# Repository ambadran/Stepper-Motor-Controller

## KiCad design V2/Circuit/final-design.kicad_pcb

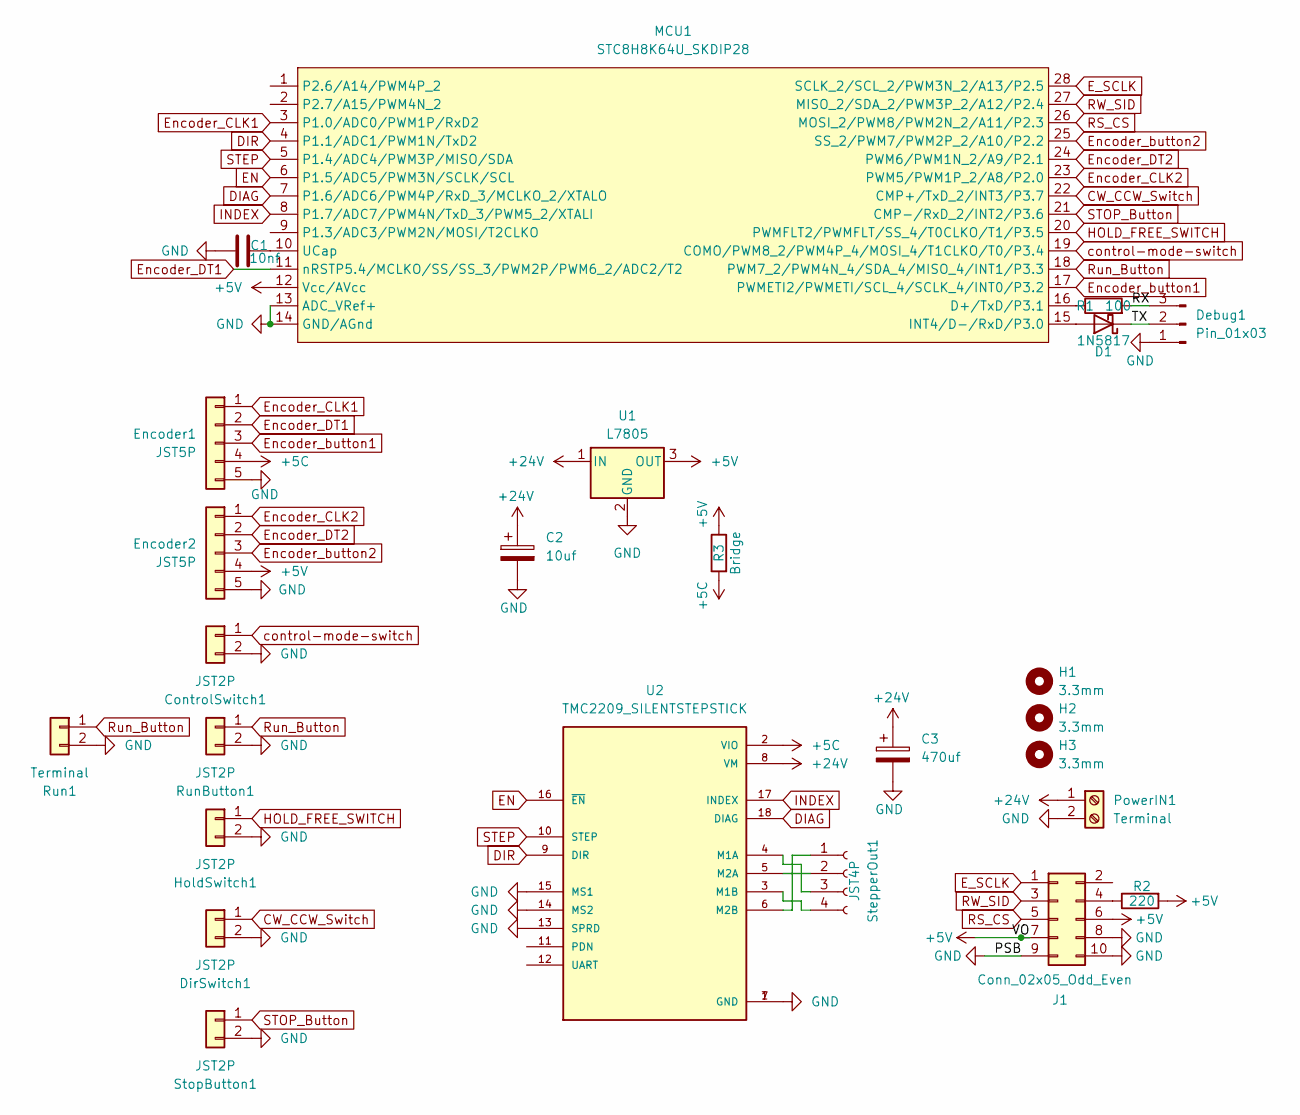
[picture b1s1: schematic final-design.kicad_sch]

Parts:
C1: 10nf; R_Axial_DIN0207_L6.3mm_D2.5mm_P7.62mm_Horizontal
C2: 10uf; CP_Radial_D5.0mm_P2.50mm
C3: 470uf; CP_Radial_D8.0mm_P3.50mm
ControlSwitch1: JST2P; JST_EH_B2B-EH-A_1x02_P2.50mm_Vertical
D1: 1N5817; D_DO-41_SOD81_P7.62mm_Horizontal
Debug1: Pin_01x03; PinHeader_1x03_P2.54mm_Vertical
DirSwitch1: JST2P; JST_EH_B2B-EH-A_1x02_P2.50mm_Vertical
Encoder1, Encoder2: JST5P; JST_EH_B5B-EH-A_1x05_P2.50mm_Vertical
H1, H2, H3: 3.3mm; MountingHole_3.2mm_M3
HoldSwitch1: JST2P; JST_EH_B2B-EH-A_1x02_P2.50mm_Vertical
J1: Conn_02x05_Odd_Even; IDC-Header_2x05_P2.54mm_Vertical
MCU1: STC8H8K64U_SKDIP28; SKDIP28
PowerIN1: Terminal; TerminalBlock_bornier-2_P5.08mm
R1: 100; R_Axial_DIN0207_L6.3mm_D2.5mm_P7.62mm_Horizontal
R2: 220; R_Axial_DIN0207_L6.3mm_D2.5mm_P7.62mm_Horizontal
R3: Bridge; R_Axial_DIN0207_L6.3mm_D2.5mm_P5.08mm_Vertical
Run1: Terminal; TerminalBlock_bornier-2_P5.08mm
RunButton1: JST2P; JST_EH_B2B-EH-A_1x02_P2.50mm_Vertical
StepperOut1: JST4P; JST_EH_B4B-EH-A_1x04_P2.50mm_Vertical
StopButton1: JST2P; JST_EH_B2B-EH-A_1x02_P2.50mm_Vertical
U1: L7805; TO-220-3_Vertical
U2: TMC2209_SILENTSTEPSTICK; MODULE_TMC2209_SILENTSTEPSTICK; PARTREV 1.20

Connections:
+5C: Encoder1.4, R3.2, U2.2 (VIO)
+5V: Encoder2.4, J1.6, J1.7, MCU1.12 (Vcc/AVcc), R2.2, R3.1, U1.3 (OUT)
+24V: C2.1, C3.1, PowerIN1.1, U1.1 (IN), U2.8 (VM)
/RX: Debug1.3, R1.2
/TX: D1.1 (K), Debug1.2
CW_CCW_Switch: DirSwitch1.1, MCU1.22 (CMP+/TxD_2/INT3/P3.7)
DIAG: MCU1.7 (P1.6/ADC6/PWM4P/RxD_3/MCLKO_2/XTALO), U2.18 (DIAG)
DIR: MCU1.4 (P1.1/ADC1/PWM1N/TxD2), U2.9 (DIR)
EN: MCU1.6 (P1.5/ADC5/PWM3N/SCLK/SCL), U2.16 (~EN)
E_SCLK: J1.1, MCU1.28 (SCLK_2/SCL_2/PWM3N_2/A13/P2.5)
Encoder_CLK1: Encoder1.1, MCU1.3 (P1.0/ADC0/PWM1P/RxD2)
Encoder_CLK2: Encoder2.1, MCU1.23 (PWM5/PWM1P_2/A8/P2.0)
Encoder_DT1: Encoder1.2, MCU1.11 (nRSTP5.4/MCLKO/SS/SS_3/PWM2P/PWM6_2/ADC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)
Encoder_DT2: Encoder2.2, MCU1.24 (PWM6/PWM1N_2/A9/P2.1)
Encoder_button1: Encoder1.3, MCU1.17 (PWMETI2/PWMETI/SCL_4/SCLK_4/INT0/P3.2)
Encoder_button2: Encoder2.3, MCU1.25 (SS_2/PWM7/PWM2P_2/A10/P2.2)
GND: C1.1, C2.2, C3.2, ControlSwitch1.2, Debug1.1, DirSwitch1.2, Encoder1.5, Encoder2.5, HoldSwitch1.2, J1.8, J1.9, J1.10, MCU1.13 (ADC_VRef+), MCU1.14 (GND/AGnd), PowerIN1.2, Run1.2, RunButton1.2, StopButton1.2, U1.2 (GND), U2.1 (GND), U2.7 (GND), U2.13 (SPRD), U2.14 (MS2), U2.15 (MS1)
HOLD_FREE_SWITCH: HoldSwitch1.1, MCU1.20 (PWMFLT2/PWMFLT/SS_4/T0CLKO/T1/P3.5)
INDEX: MCU1.8 (P1.7/ADC7/PWM4N/TxD_3/PWM5_2/XTALI), U2.17 (INDEX)
unnamed: D1.2 (A), MCU1.15 (INT4/D-/RxD/P3.0)
unnamed: J1.4, R2.1
unnamed: MCU1.16 (D+/TxD/P3.1), R1.1
unnamed: C1.2, MCU1.10 (UCap)
unnamed: StepperOut1.1, U2.6 (M2B)
unnamed: StepperOut1.2, U2.5 (M2A)
unnamed: StepperOut1.3, U2.4 (M1A)
unnamed: StepperOut1.4, U2.3 (M1B)
RS_CS: J1.5, MCU1.26 (MOSI_2/PWM8/PWM2N_2/A11/P2.3)
RW_SID: J1.3, MCU1.27 (MISO_2/SDA_2/PWM3P_2/A12/P2.4)
Run_Button: MCU1.18 (PWM7_2/PWM4N_4/SDA_4/MISO_4/INT1/P3.3), Run1.1, RunButton1.1
STEP: MCU1.5 (P1.4/ADC4/PWM3P/MISO/SDA), U2.10 (STEP)
STOP_Button: MCU1.21 (CMP-/RxD_2/INT2/P3.6), StopButton1.1
control-mode-switch: ControlSwitch1.1, MCU1.19 (COMO/PWM8_2/PWM4P_4/MOSI_4/T1CLKO/T0/P3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)

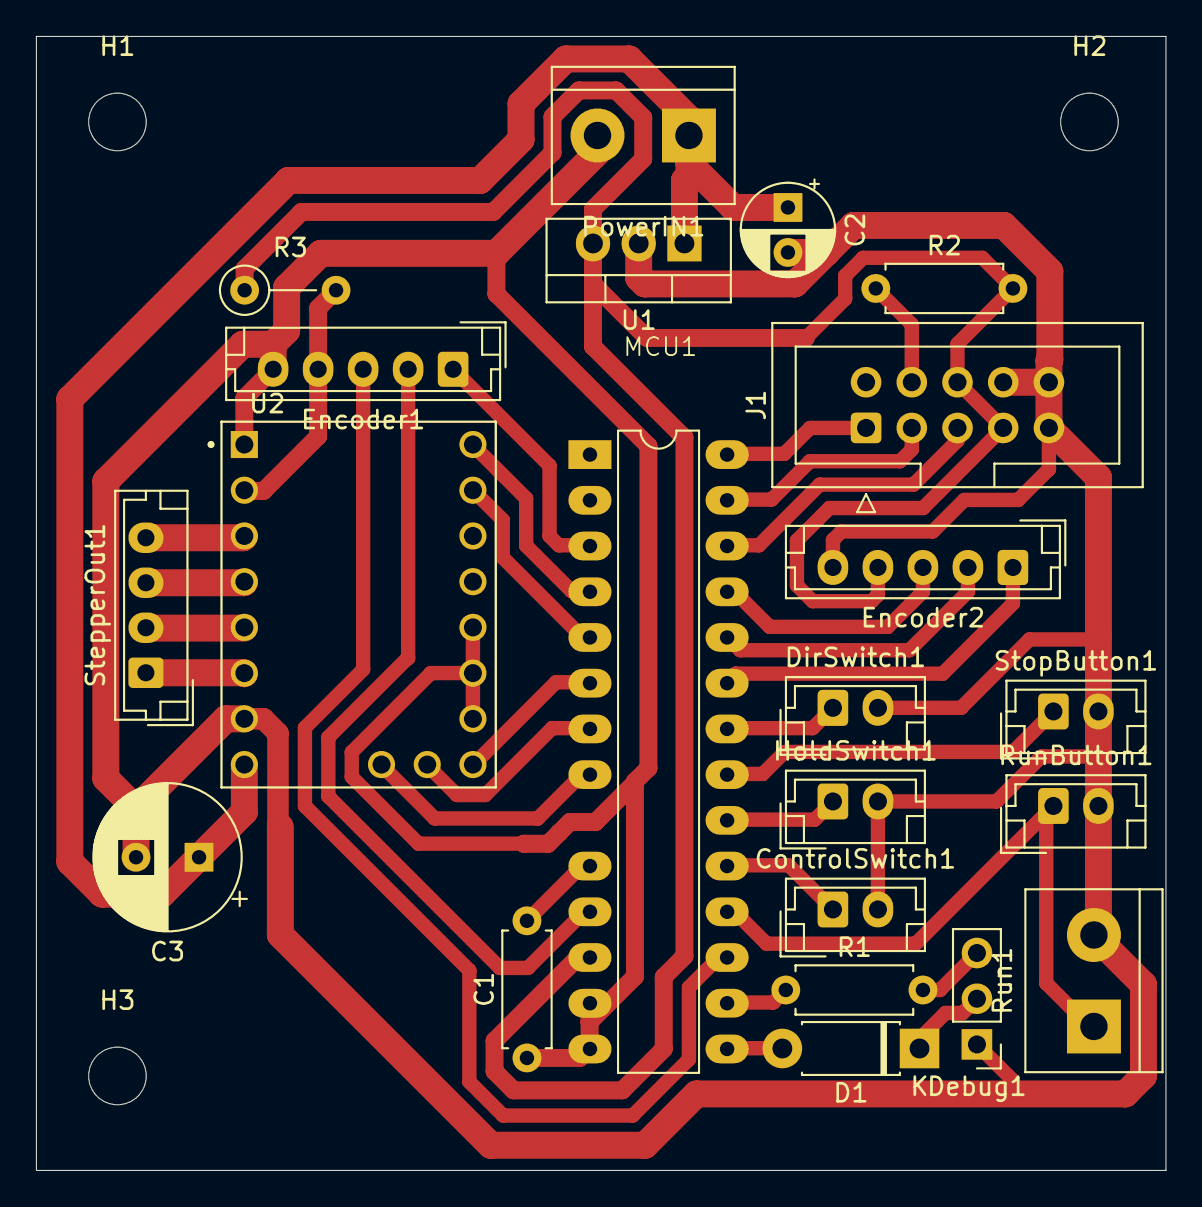
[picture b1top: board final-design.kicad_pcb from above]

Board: 2 copper layers, 62.8 x 63.0 mm, 25 parts (0 on the bottom side), 33 nets.

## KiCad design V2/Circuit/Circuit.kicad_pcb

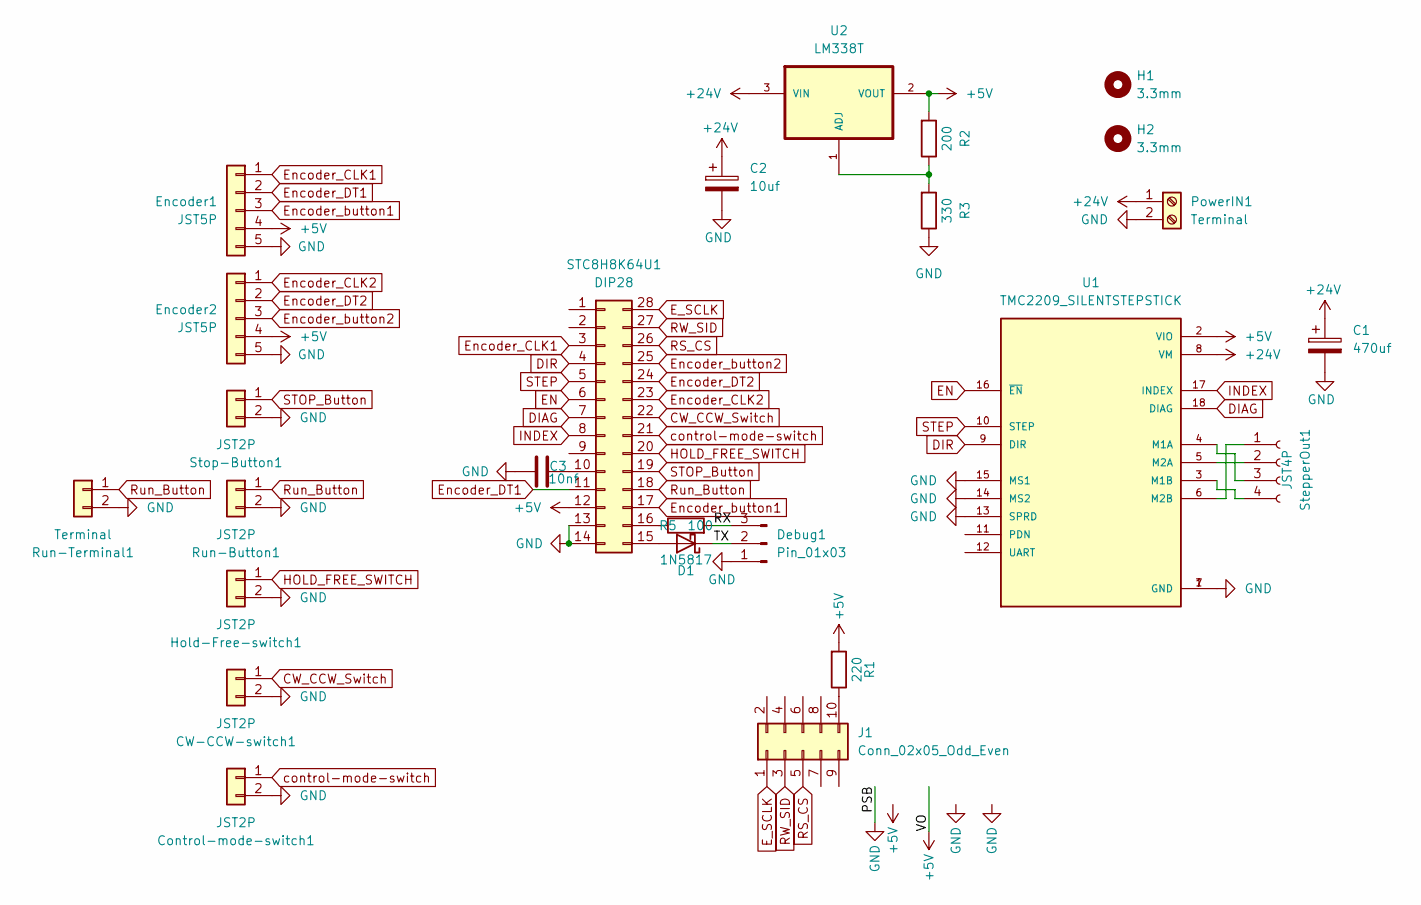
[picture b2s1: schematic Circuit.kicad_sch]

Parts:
C1: 470uf; CP_Radial_D8.0mm_P3.50mm
C2: 10uf; CP_Radial_D5.0mm_P2.50mm
C3: 10nf; R_Axial_DIN0207_L6.3mm_D2.5mm_P7.62mm_Horizontal
CW-CCW-switch1: JST2P; JST_EH_B2B-EH-A_1x02_P2.50mm_Vertical
Control-mode-switch1: JST2P; JST_EH_B2B-EH-A_1x02_P2.50mm_Vertical
D1: 1N5817; D_DO-41_SOD81_P7.62mm_Horizontal
Debug1: Pin_01x03; PinHeader_1x03_P2.54mm_Vertical
Encoder1, Encoder2: JST5P; JST_EH_B5B-EH-A_1x05_P2.50mm_Vertical
H1, H2: 3.3mm; MountingHole_3.2mm_M3
Hold-Free-switch1: JST2P; JST_EH_B2B-EH-A_1x02_P2.50mm_Vertical
J1: Conn_02x05_Odd_Even; IDC-Header_2x05_P2.54mm_Vertical
PowerIN1: Terminal; TerminalBlock_bornier-2_P5.08mm
R1: 220; R_Axial_DIN0207_L6.3mm_D2.5mm_P7.62mm_Horizontal
R2: 200; R_Axial_DIN0207_L6.3mm_D2.5mm_P7.62mm_Horizontal
R3: 330; R_Axial_DIN0207_L6.3mm_D2.5mm_P7.62mm_Horizontal
R5: 100; R_Axial_DIN0207_L6.3mm_D2.5mm_P7.62mm_Horizontal
Run-Button1: JST2P; JST_EH_B2B-EH-A_1x02_P2.50mm_Vertical
Run-Terminal1: Terminal; TerminalBlock_bornier-2_P5.08mm
STC8H8K64U1: DIP28; DIP-28_W7.62mm_Socket_LongPads
StepperOut1: JST4P; JST_EH_B4B-EH-A_1x04_P2.50mm_Vertical
Stop-Button1: JST2P; JST_EH_B2B-EH-A_1x02_P2.50mm_Vertical
U1: TMC2209_SILENTSTEPSTICK; MODULE_TMC2209_SILENTSTEPSTICK; PARTREV 1.20
U2: LM338T; TO254P1054X470X1955-3

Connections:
+5V: Encoder1.4, Encoder2.4, R1.2, R2.2, STC8H8K64U1.12, U1.2 (VIO), U2.2 (VOUT); also elsewhere on the board
+24V: C1.1, C2.1, PowerIN1.1, U1.8 (VM), U2.3 (VIN)
/RX: Debug1.3, R5.2
/TX: D1.1 (K), Debug1.2
CW_CCW_Switch: CW-CCW-switch1.1, STC8H8K64U1.22
DIAG: STC8H8K64U1.7, U1.18 (DIAG)
DIR: STC8H8K64U1.4, U1.9 (DIR)
EN: STC8H8K64U1.6, U1.16 (~EN)
E_SCLK: J1.1, STC8H8K64U1.28; also elsewhere on the board
Encoder_CLK1: Encoder1.1, STC8H8K64U1.3
Encoder_CLK2: Encoder2.1, STC8H8K64U1.23
Encoder_DT1: Encoder1.2, STC8H8K64U1.11
Encoder_DT2: Encoder2.2, STC8H8K64U1.24
Encoder_button1: Encoder1.3, STC8H8K64U1.17
Encoder_button2: Encoder2.3, STC8H8K64U1.25
GND: C1.2, C2.2, C3.1, CW-CCW-switch1.2, Control-mode-switch1.2, Debug1.1, Encoder1.5, Encoder2.5, Hold-Free-switch1.2, PowerIN1.2, R3.1, Run-Button1.2, Run-Terminal1.2, STC8H8K64U1.13, STC8H8K64U1.14, Stop-Button1.2, U1.1 (GND), U1.7 (GND), U1.13 (SPRD), U1.14 (MS2), U1.15 (MS1); also elsewhere on the board
HOLD_FREE_SWITCH: Hold-Free-switch1.1, STC8H8K64U1.20
INDEX: STC8H8K64U1.8, U1.17 (INDEX)
unnamed: D1.2 (A), STC8H8K64U1.15
unnamed 19: J1.10, R1.1; also elsewhere on the board
unnamed: C3.2, STC8H8K64U1.10
unnamed: R5.1, STC8H8K64U1.16
unnamed: StepperOut1.1, U1.6 (M2B)
unnamed: StepperOut1.2, U1.5 (M2A)
unnamed: StepperOut1.3, U1.4 (M1A)
unnamed: StepperOut1.4, U1.3 (M1B)
unnamed: R2.1, R3.2, U2.1 (ADJ)
RS_CS: J1.5, STC8H8K64U1.26; also elsewhere on the board
RW_SID: J1.3, STC8H8K64U1.27; also elsewhere on the board
Run_Button: Run-Button1.1, Run-Terminal1.1, STC8H8K64U1.18
STEP: STC8H8K64U1.5, U1.10 (STEP)
STOP_Button: STC8H8K64U1.19, Stop-Button1.1
control-mode-switch: Control-mode-switch1.1, STC8H8K64U1.21

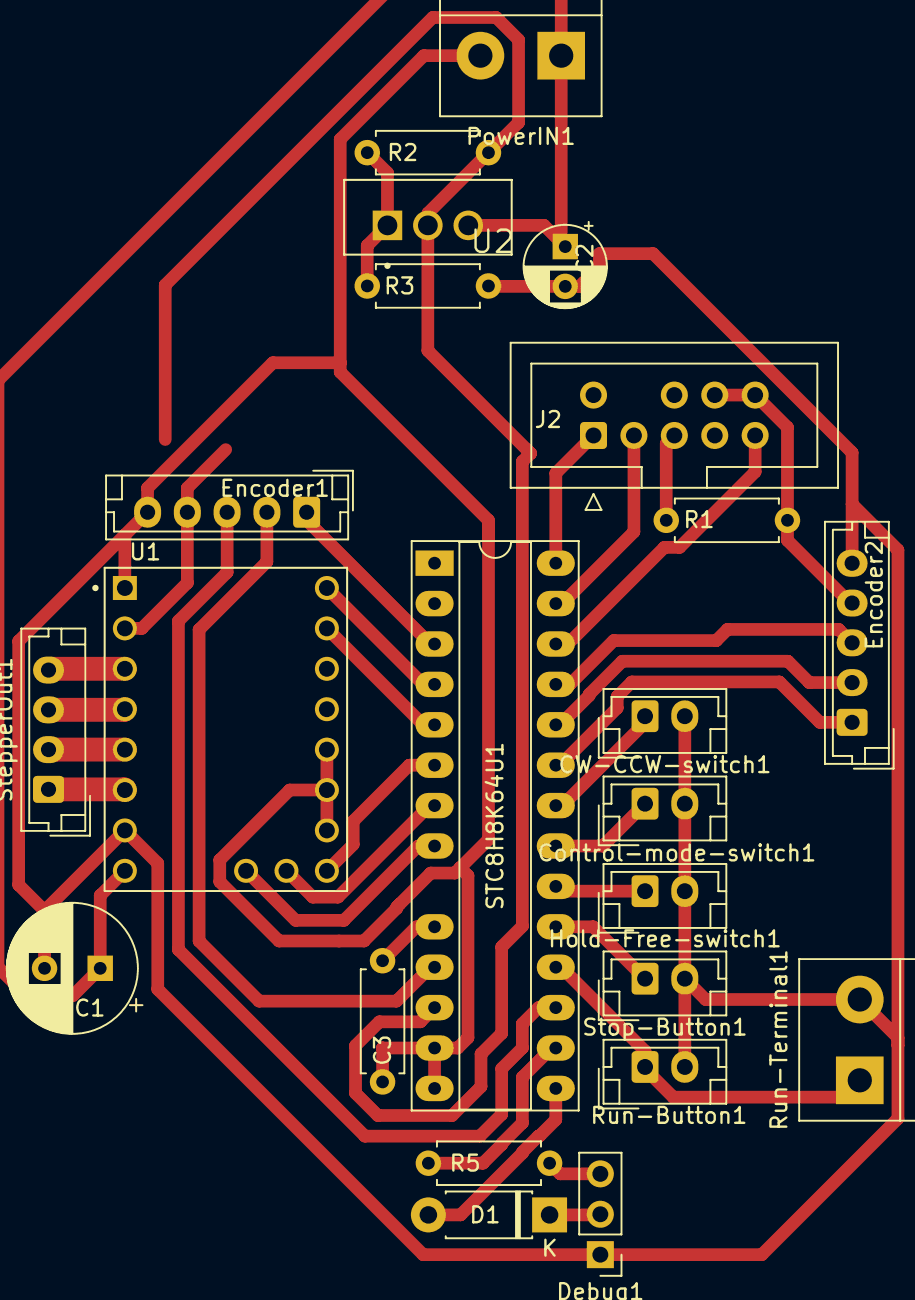
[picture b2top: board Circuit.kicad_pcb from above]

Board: 2 copper layers, 25 parts (0 on the bottom side), 33 nets.

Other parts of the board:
J2: IDC-10P; IDC-Header_2x05_P2.54mm_Vertical

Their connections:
+5V: J2.8, J2.10; also elsewhere on the board
E_SCLK: J2.1; also elsewhere on the board
GND: J2.2, J2.6, J2.7; also elsewhere on the board
unnamed 19: J2.5; also elsewhere on the board
RS_CS: J2.9; also elsewhere on the board
RW_SID: J2.3; also elsewhere on the board

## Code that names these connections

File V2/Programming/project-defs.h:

#ifndef PROJECT_DEFS
#define PROJECT_DEFS

/* Console settings */
#define CONSOLE_SPEED 115200
#define CONSOLE_UART UART1
#define CONSOLE_PIN_CONFIG 0

/* gpio-hal Settings */
// ***Right Side Pins Mappings*** //
#define E_SCLK_PORT GPIO_PORT2
#define E_SCLK_PIN GPIO_PIN5
#define RW_SID_PORT GPIO_PORT2
#define RW_SID_PIN GPIO_PIN4
#define RS_CS_PORT GPIO_PORT2
#define RS_CS_PIN GPIO_PIN3
#define ENCODER2_BUTTON_PORT GPIO_PORT2
#define ENCODER2_BUTTON_PIN GPIO_PIN2
#define ENCODER2_DT_PORT GPIO_PORT2
#define ENCODER2_DT_PIN GPIO_PIN1
#define ENCODER2_CLK_PORT GPIO_PORT2
#define ENCODER2_CLK_PIN GPIO_PIN0
#define CW_CCW_SWITCH_PORT GPIO_PORT3
#define CW_CCW_SWITCH_PIN GPIO_PIN7
#define STOP_BUTTON_PORT GPIO_PORT3
#define STOP_BUTTON_PIN GPIO_PIN6
#define HOLD_FREE_SWITCH_PORT GPIO_PORT3
#define HOLD_FREE_SWITCH_PIN GPIO_PIN5
#define CONTROL_MODE_SWITCH_PORT GPIO_PORT3
#define CONTROL_MODE_SWITCH_PIN GPIO_PIN4
#define RUN_PAUSE_BUTTON_PORT GPIO_PORT3
#define RUN_PAUSE_BUTTON_PIN GPIO_PIN3
#define ENCODER1_BUTTON_PORT GPIO_PORT3
#define ENCODER1_BUTTON_PIN GPIO_PIN2
// P3.1/TX -> Programming/Debugging
// P3.0/RX -> Programming/Debugging

// ***Left Side Pins Mappings*** //
#define ENCODER1_CLK_PORT GPIO_PORT1
#define ENCODER1_CLK_PIN GPIO_PIN0
#define STEPPER_PORT GPIO_PORT1
#define STEPPER_DIR_PIN GPIO_PIN1
#define STEPPER_STEP_PIN GPIO_PIN4
#define STEPPER_ENABLE_PIN GPIO_PIN5
#define STEPPER_DIAG_PIN GPIO_PIN6
#define STEPPER_INDEX_PIN GPIO_PIN7
#define ENCODER1_DT_PORT GPIO_PORT5
#define ENCODER1_DT_PIN GPIO_PIN4

// external pin INTERRUPTS
/* #define STOP_BUTTON_PIN_ISR extint2_isr */
/* #define STOP_BUTTON_PIN_INTERRUPT EXTINT2_INTERRUPT */

/* advpwm-hal Settings */
#define HAL_PWM_API_QUADRATURE_ENCODER
// For PWM_COUNTER_A, we use PWM1P and PWM2P on P1.0 and P5.4 (pin switch = 0).
#define ENCODER1_COUNTER PWM_COUNTER_A
#define ENCODER1_PWM_PIN_SWITCH  0
#define ENCODER1_CHANNEL PWM_Channel0
// For PWM_COUNTER_B, we use PWM5 and PWM6 on P2.0 and P2.1 (pin switch = 0).
#define ENCODER2_COUNTER PWM_COUNTER_B
#define ENCODER2_PWM_PIN_SWITCH  0
#define ENCODER2_CHANNEL PWM_Channel4

/* timer-hal configs */
#define HAL_TIMER_API_STOP_TIMER
#define STEPPER_TIMER TIMER0
#define STEPPER_TIMER_ISR timer0_isr
#define STEPPER_TIMER_INTERRUPT TIMER0_INTERRUPT
// timer 3 acts super weird. where it's fast at specific values and slow at others?!?!
#define GLOBAL_TIMER TIMER3
#define GLOBAL_TIMER_ISR timer3_isr
#define GLOBAL_TIMER_INTERRUPT TIMER3_INTERRUPT

/* Button HAL Defaults */
#define BUTTON_COOLDOWN_PERIOD 300 // time in ms to stop reading button if pressed
#define ENCODER_INITIAL_DELAY 1
#define ENCODER_COOLDOWN_PERIOD 4 // time in ms to stop reading encoder if pressed

/* Stepper Motor HAL Defaults */
#define USER_FREQ_TO_STEPPER_FREQ 200 // since 20000/100 equals 200

#define ANGLE_VALUE_DIGIT_NUM 5 // 000000
#define SPEED_VALUE_DIGIT_NUM 3 // 000

#define DEFAULT_STEP_NUM 16560 // one revolution
#define DEFAULT_STEPPER_FREQUENCY 8000
#define DEFAULT_ANGLE_TO_STEPS 46.00

#define DEFAULT_ENCODER_CONTROL_FREQ 7000

#define STEPPER_MIN_FREQ 50
#define STEPPER_MAX_FREQ 20000
#define USER_MIN_FREQ 1
#define USER_MAX_FREQ 100

#define DEG_STEP_DIGIT_NUM 5 // 000.00

/* includes */
#include <STC/8H8KxxU/SKDIP28.h>
#include <stdio.h>
#include <stdint.h>
#include <string.h>
#include <delay.h>
#include <gpio-hal.h>
#include <lcd/links/lcd-link-serial.h>
#include <lcd/lcd-device.h>
#include <lcd/lcd-text.h>
#include <uart-hal.h>
#include <serial-console.h>
#include <timer-hal.h>
#include "global_timer.h"
#include "stepper_driver.h"
#include "encoder.h"
#include "buttons.h"
#include "switch.h"
#include "display.h"
#include "nuts_bolts.h"
#include "application.h"

#endif

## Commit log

2025-01-06 added V1 files
2025-01-06 Started V2
2025-01-07 further dev in BOM and schematics
2025-01-08 added IDC connection for LCD and started programming, added gitignore and attribute
2025-01-08 added control mode switch
2025-01-10 changed main MCU and started Programming
2025-01-11 finished pin mapping and most of HAL layer Programming
2025-01-11 Finshed all HAL and a good chunk of application layer, finalized circuit schematic
2025-01-11 almost finished pcb tracing
2025-01-12 modified gitignore
2025-01-12 finished PCB layout
2025-01-13 minor changes in circuit and more dev in programming
2025-01-13 further development in application layer
2025-01-14 new flawless encoder interfacing and single digit control for both encoders implemented
2025-01-15 further dev in application layer
2025-01-15 lots of bug fixes and further dev in application layer
2025-01-16 FINALLY SOLVED THE LCD PROBLEM! and finished step control mode
2025-01-17 finished most encoder mode
2025-01-18 finished all application layer
2025-01-18 fixed float precision bug error
2025-01-26 minor circuit changes
2025-01-27 upgraded board to use l7805 instead of lm317
2025-01-30 removed old pdfs
2025-01-31 minor settings tuning
